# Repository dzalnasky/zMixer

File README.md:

# zMixer
zMixer is a USB-C programmable, 0-4GHz IF to 5-10.4GHz RF upconverting/downconverting RF mixer with dedicated LO chip generating 0-6.4GHz. Perfect for radios with operating frequencies up to 4GHz that want to work with higher frequency bands. 
# Key Components
* Texas Instruments LMX2572 Frequency Synthesizer
  * Drop in replacements include the LMX2592 (up to 9.8GHz), LMX2594 (up to 15GHz), and LMX2595 (up to 20GHz) for higher LO frequency generation **(May require different RF mixer IC)*
* Microchip MCP2210 USB to SPI Interface
* Analog Devices HMC220B RF Mixer
  * Drop in replacement includes HMC218B (3.5-8GHz RF/LO, 1.5GHz IF)
# Block Diagram

# Schematic

# PCB

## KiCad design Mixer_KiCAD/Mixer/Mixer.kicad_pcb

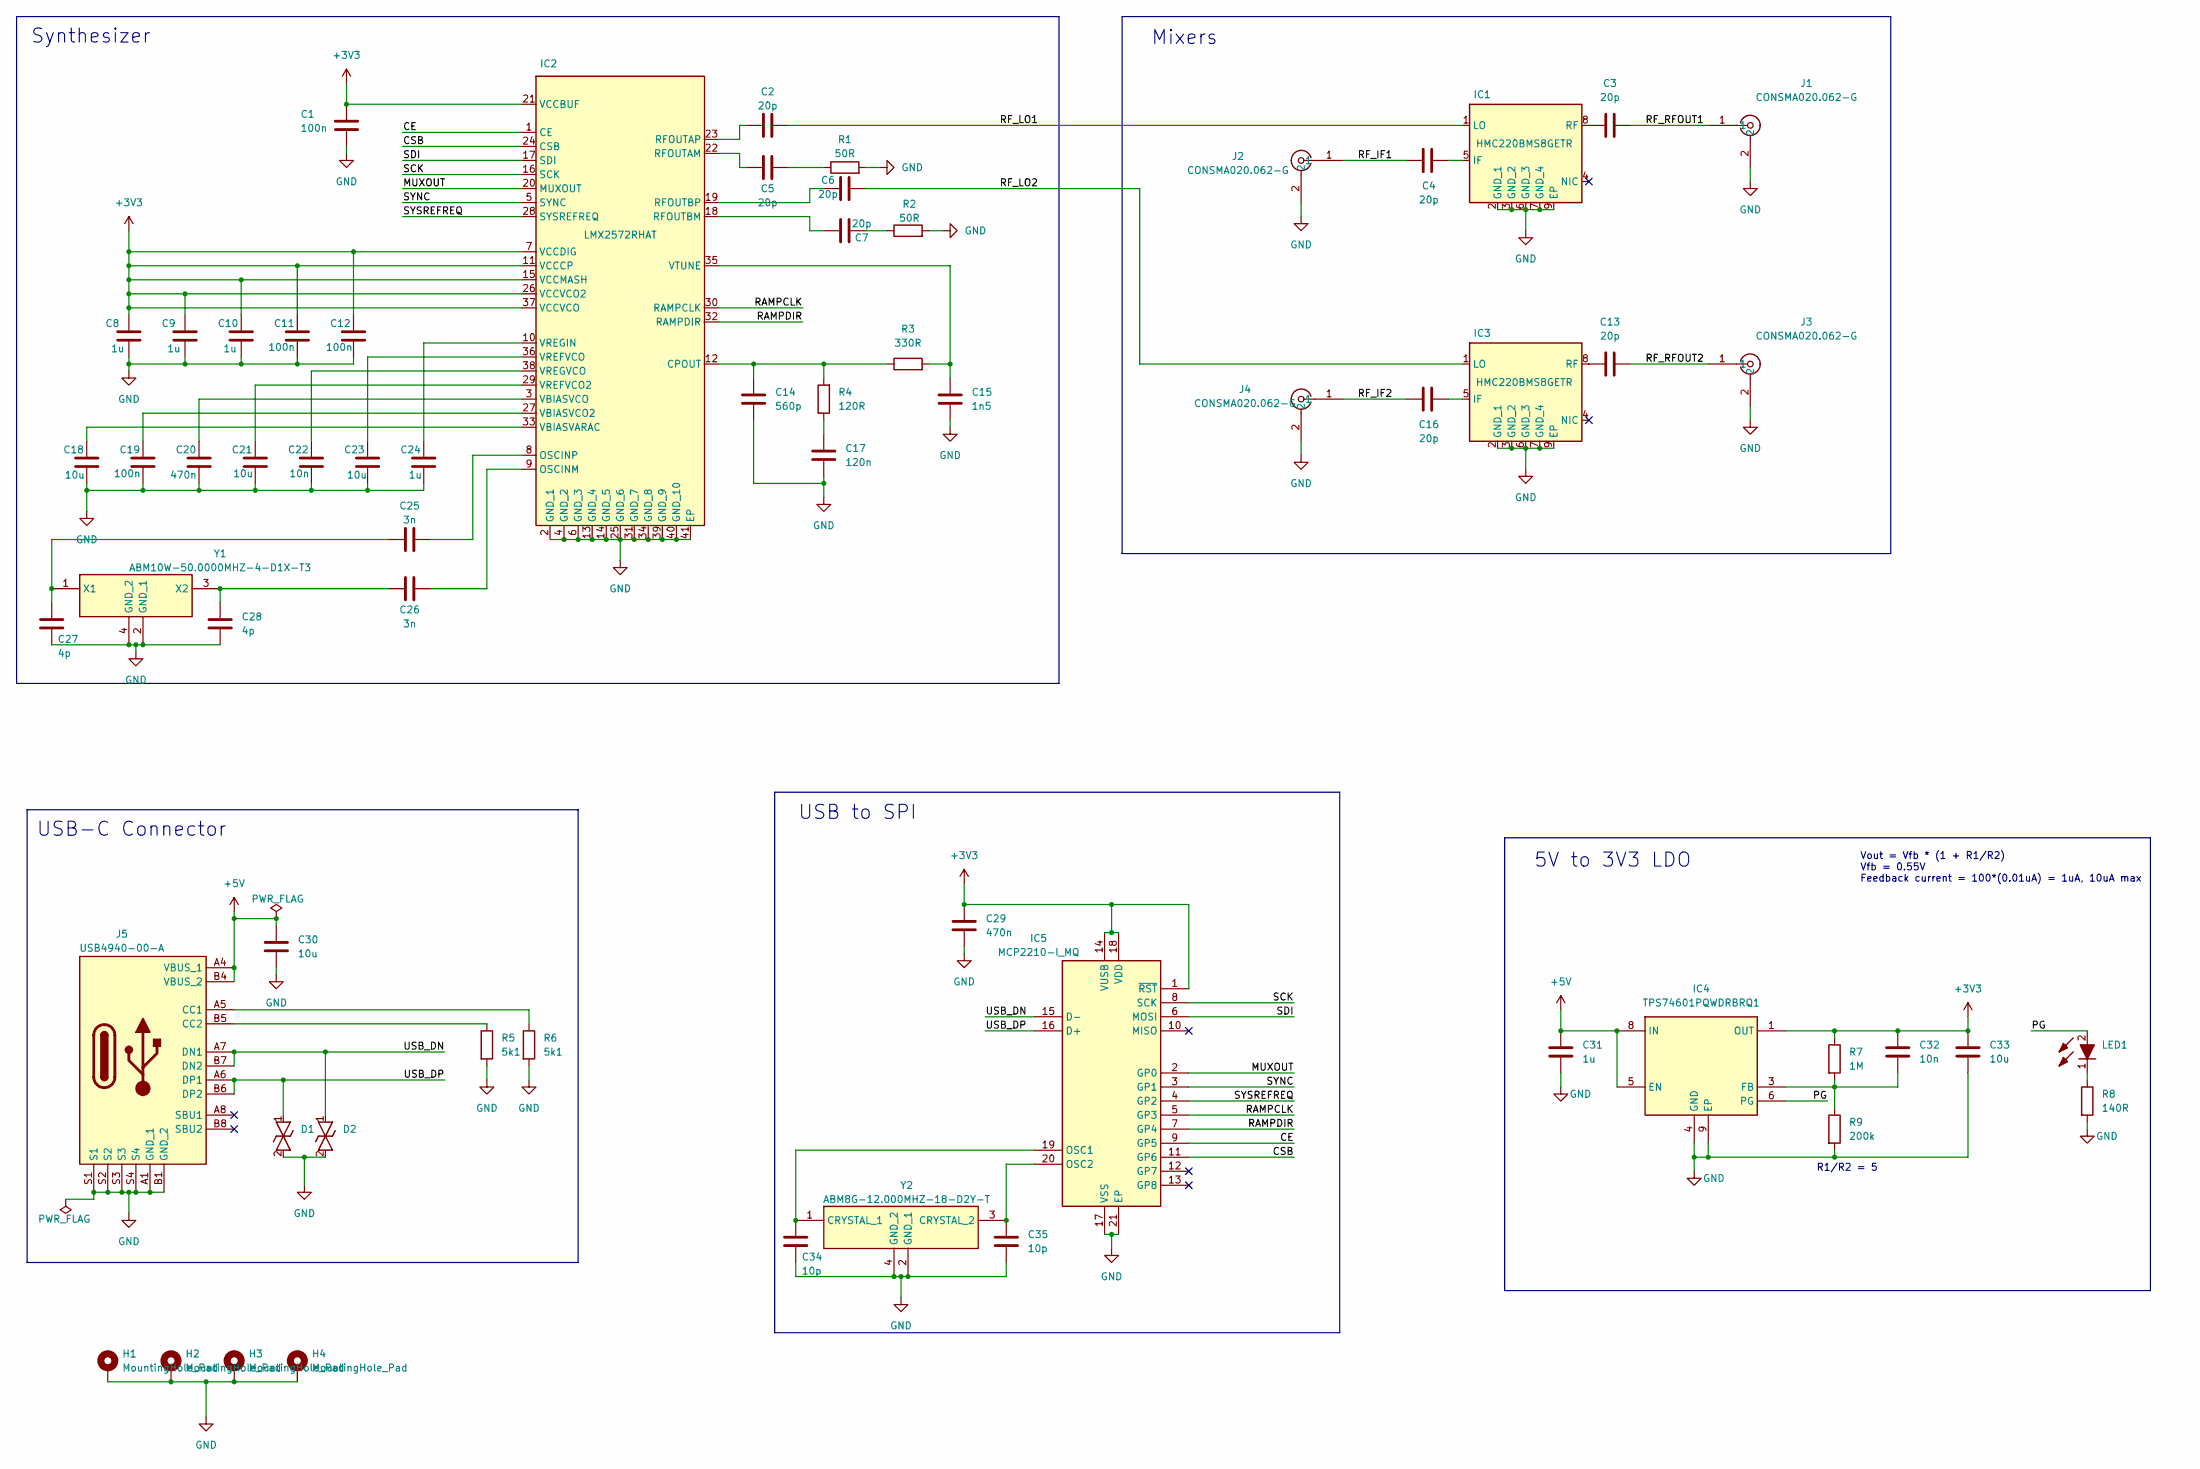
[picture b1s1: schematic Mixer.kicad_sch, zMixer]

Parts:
C1, C11, C12, C19: 100n; C_0402_1005Metric_Pad0.74x0.62mm_HandSolder; Voltage/Current Rating 6.3V
C2, C3, C4, C5, C6, C7, C13, C16: 20p; C_0402_1005Metric_Pad0.74x0.62mm_HandSolder
C8, C9, C10, C24: 1u; C_0402_1005Metric_Pad0.74x0.62mm_HandSolder; Voltage/Current Rating 6.3V
C14: 560p; C_0402_1005Metric_Pad0.74x0.62mm_HandSolder; Voltage/Current Rating 6.3V
C15: 1n5; C_0402_1005Metric_Pad0.74x0.62mm_HandSolder; Voltage/Current Rating 6.3V
C17: 120n; C_0402_1005Metric_Pad0.74x0.62mm_HandSolder; Voltage/Current Rating 6.3V
C18, C21, C23, C30: 10u; C_0603_1608Metric_Pad1.08x0.95mm_HandSolder; Voltage/Current Rating 6.3V
C20: 470n; C_0402_1005Metric_Pad0.74x0.62mm_HandSolder; Voltage/Current Rating 6.3V
C22: 10n; C_0402_1005Metric_Pad0.74x0.62mm_HandSolder; Voltage/Current Rating 6.3V
C25, C26: 3n; C_0402_1005Metric_Pad0.74x0.62mm_HandSolder
C27, C28: 4p; C_0402_1005Metric_Pad0.74x0.62mm_HandSolder
C29: 470n; C_0402_1005Metric_Pad0.74x0.62mm_HandSolder
C31: 1u; C_0402_1005Metric_Pad0.74x0.62mm_HandSolder
C32: 10n; C_0402_1005Metric_Pad0.74x0.62mm_HandSolder
C33: 10u; C_0603_1608Metric_Pad1.08x0.95mm_HandSolder
C34, C35: 10p; C_0402_1005Metric_Pad0.74x0.62mm_HandSolder
D1, D2: ESD8472MUT5G; X3DFN2-CASE152AF-ISSUE-A; Mouser Part Number 863-ESD8472MUT5G
H1, H2, H3, H4: MountingHole_Pad; MountingHole_2.2mm_M2_Pad_TopBottom
IC1, IC3: HMC220BMS8GETR; SOP65P490X110-9N; Manufacturer_Part_Number HMC220BMS8GETR; Mouser Part Number 584-HMC220BMS8GETR
IC2: LMX2572RHAT; QFN50P600X600X100-41N-D; Mouser Part Number 595-LMX2572RHAT
IC4: TPS74601PQWDRBRQ1; SON65P300X300X100-9N-D; Manufacturer_Part_Number TPS74601PQWDRBRQ1
IC5: MCP2210-I_MQ; QFN65P500X500X100-21N-D; Mouser Part Number 579-MCP2210IMQ
J1, J2, J3, J4: CONSMA020.062-G; CONSMA020062G; Mouser Part Number 712-CONSMA020.062-G
J5: USB4940-00-A; USB494000A; Manufacturer_Part_Number USB4940-00-A
LED1: SML-D12U1WT86; LEDC1608X65N; Mouser Part Number 755-SML-D12U1WT86
R1, R2: 50R; R_0603_1608Metric_Pad0.98x0.95mm_HandSolder
R3: 330R; R_0603_1608Metric_Pad0.98x0.95mm_HandSolder
R4: 120R; R_0603_1608Metric_Pad0.98x0.95mm_HandSolder
R5, R6: 5k1; R_0603_1608Metric_Pad0.98x0.95mm_HandSolder
R7: 1M; R_0603_1608Metric_Pad0.98x0.95mm_HandSolder
R8: 140R; R_0603_1608Metric_Pad0.98x0.95mm_HandSolder
R9: 200k; R_0603_1608Metric_Pad0.98x0.95mm_HandSolder
Y1: ABM10W-50.0000MHZ-4-D1X-T3; ABM10W240000MHZ8K1ZT3; Mouser Part Number 815-10W50-4D1XT
Y2: ABM8G-12.000MHZ-18-D2Y-T; ABM8G12000MHZ18D2YT; Mouser Part Number 815-ABM8G-12-18D2Y

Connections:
+3V3: C1.1, C8.1, C9.1, C10.1, C11.1, C12.1, C29.1, C32.1, C33.1, IC2.7 (VCCDIG), IC2.11 (VCCCP), IC2.15 (VCCMASH), IC2.21 (VCCBUF), IC2.26 (VCCVCO2), IC2.37 (VCCVCO), IC4.1 (OUT), IC5.1 (~RST), IC5.14 (VUSB), IC5.18 (VDD), R7.1
+5V: C30.1, C31.1, IC4.5 (EN), IC4.8 (IN), J5.A4 (VBUS_1), J5.B4 (VBUS_2)
/CE: IC2.1 (CE), IC5.9 (GP5)
/CSB: IC2.24 (CSB), IC5.11 (GP6)
/MUXOUT: IC2.20 (MUXOUT), IC5.2 (GP0)
/PG: IC4.6 (PG), LED1.2 (A)
/RAMPCLK: IC2.30 (RAMPCLK), IC5.5 (GP3)
/RAMPDIR: IC2.32 (RAMPDIR), IC5.7 (GP4)
/RF_IF1: C4.1, J2.1
/RF_IF2: C16.1, J4.1
/RF_LO1: C2.2, IC1.1 (LO)
/RF_LO2: C6.2, IC3.1 (LO)
/RF_RFOUT1: C3.2, J1.1
/RF_RFOUT2: C13.2, J3.1
/SCK: IC2.16 (SCK), IC5.8 (SCK)
/SDI: IC2.17 (SDI), IC5.6 (MOSI)
/SYNC: IC2.5 (SYNC), IC5.3 (GP1)
/SYSREFREQ: IC2.28 (SYSREFREQ), IC5.4 (GP2)
/USB_DN: D2.1, IC5.15 (D-), J5.A7 (DN1), J5.B7 (DN2)
/USB_DP: D1.1, IC5.16 (D+), J5.A6 (DP1), J5.B6 (DP2)
GND: C1.2, C8.2, C9.2, C10.2, C11.2, C12.2, C14.2, C15.2, C17.2, C18.2, C19.2, C20.2, C21.2, C22.2, C23.2, C24.2, C27.2, C28.2, C29.2, C30.2, C31.2, C33.2, C34.2, C35.2, D1.2, D2.2, H1.1, H2.1, H3.1, H4.1, IC1.2 (GND_1), IC1.3 (GND_2), IC1.6 (GND_3), IC1.7 (GND_4), IC1.9 (EP), IC2.2 (GND_1), IC2.4 (GND_2), IC2.6 (GND_3), IC2.13 (GND_4), IC2.14 (GND_5), IC2.25 (GND_6), IC2.31 (GND_7), IC2.34 (GND_8), IC2.39 (GND_9), IC2.40 (GND_10), IC2.41 (EP), IC3.2 (GND_1), IC3.3 (GND_2), IC3.6 (GND_3), IC3.7 (GND_4), IC3.9 (EP), IC4.4 (GND), IC4.9 (EP), IC5.17 (VSS), IC5.21 (EP), J1.2, J1.3, J2.2, J2.3, J3.2, J3.3, J4.2, J4.3, J5.A1 (GND_1), J5.B1 (GND_2), J5.S1, J5.S2, J5.S3, J5.S4, R1.2, R2.2, R5.2, R6.2, R8.2, R9.2, Y1.2 (GND_1), Y1.4 (GND_2), Y2.2 (GND_1), Y2.4 (GND_2)
unnamed: C5.2, R1.1
unnamed: C7.1, R2.1
unnamed: C17.1, R4.1
unnamed: C4.2, IC1.5 (IF)
unnamed: C3.1, IC1.8 (RF)
unnamed: C14.1, IC2.12 (CPOUT), R3.1, R4.2
unnamed: C26.2, IC2.9 (OSCINM)
unnamed: C25.2, IC2.8 (OSCINP)
unnamed: C5.1, IC2.22 (RFOUTAM)
unnamed: C2.1, IC2.23 (RFOUTAP)
unnamed: C7.2, IC2.18 (RFOUTBM)
unnamed: C6.1, IC2.19 (RFOUTBP)
unnamed: C18.1, IC2.33 (VBIASVARAC)
unnamed: C19.1, IC2.27 (VBIASVCO2)
unnamed: C20.1, IC2.3 (VBIASVCO)
unnamed: C21.1, IC2.29 (VREFVCO2)
unnamed: C23.1, IC2.36 (VREFVCO)
unnamed: C24.1, IC2.10 (VREGIN)
unnamed: C22.1, IC2.38 (VREGVCO)
unnamed: C15.1, IC2.35 (VTUNE), R3.2
unnamed: C16.2, IC3.5 (IF)
unnamed: C13.1, IC3.8 (RF)
unnamed: C32.2, IC4.3 (FB), R7.2, R9.1
unnamed: C34.1, IC5.19 (OSC1), Y2.1 (CRYSTAL_1)
unnamed: C35.1, IC5.20 (OSC2), Y2.3 (CRYSTAL_2)
unnamed: J5.A5 (CC1), R6.1
unnamed: J5.B5 (CC2), R5.1
unnamed: LED1.1 (K), R8.1
unnamed: C25.1, C27.1, Y1.1 (X1)
unnamed: C26.1, C28.1, Y1.3 (X2)

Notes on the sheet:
USB to SPI
Synthesizer
USB-C Connector
Mixers
Vout = Vfb * (1 + R1/R2) Vfb = 0.55V Feedback current = 100*(0.01uA) = 1uA, 10uA max
5V to 3V3 LDO
R1/R2 = 5

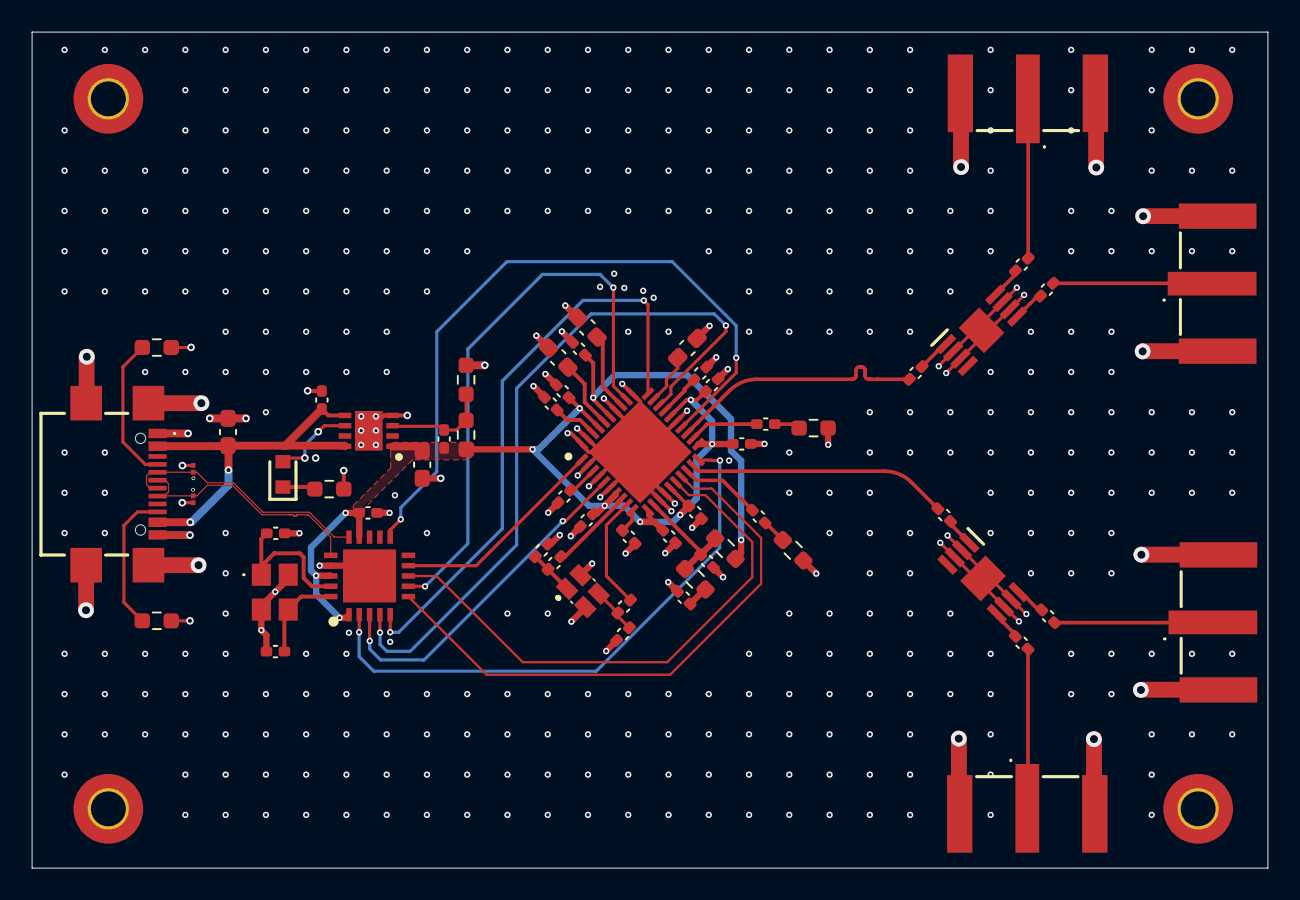
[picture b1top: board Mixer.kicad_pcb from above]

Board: 4 copper layers, 78.0 x 52.7 mm, 63 parts (0 on the bottom side), 51 nets.

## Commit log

2026-03-27 updated gerbers. updated RF trace width
2026-03-28 schematic, pcb pdfs, 3d pcb png
2026-03-30 added stitching vias to pcb
2026-04-02 adjusted RF trace width
2026-04-02 updated BOM
